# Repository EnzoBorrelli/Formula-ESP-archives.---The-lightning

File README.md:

# Formula-ESP-archives.---The-lightning
que hacer= descripcion

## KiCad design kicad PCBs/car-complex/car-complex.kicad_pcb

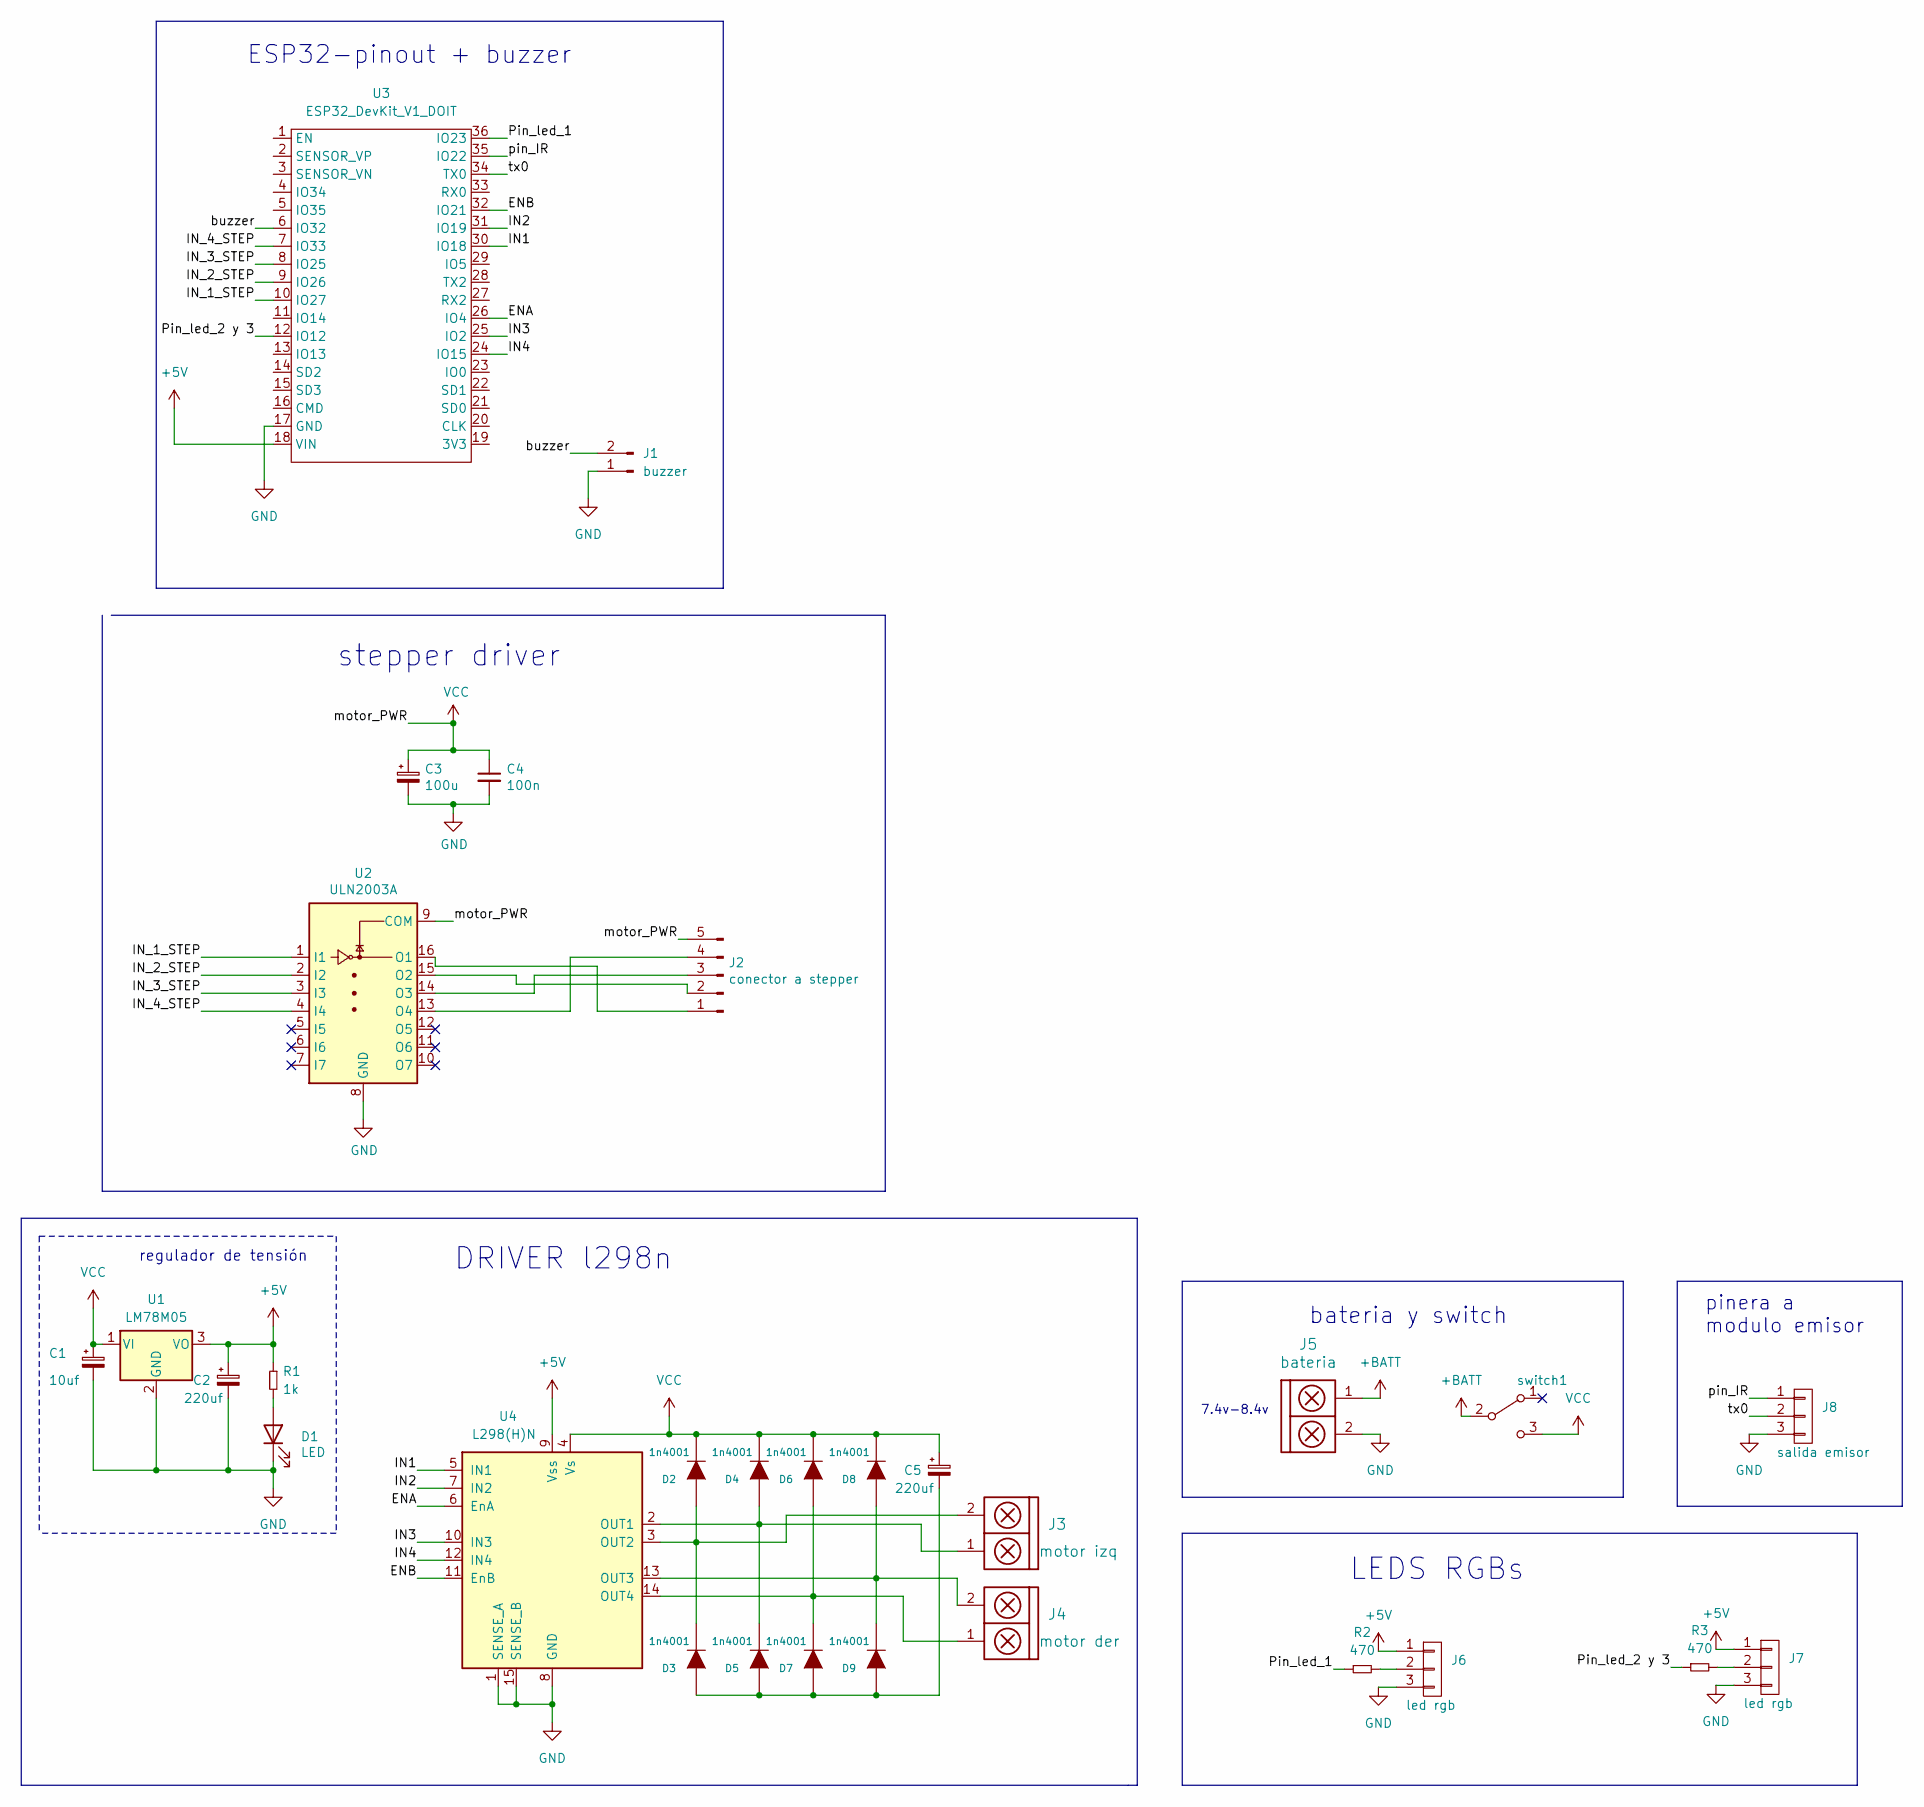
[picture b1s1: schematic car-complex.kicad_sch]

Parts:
C1: 10uf; CP_Radial_D5.0mm_P2.00mm
C2, C5: 220uf; CP_Radial_D5.0mm_P2.00mm
C3: 100u; CP_Radial_D5.0mm_P2.00mm
C4: 100n; C_Rect_L4.6mm_W2.0mm_P2.50mm_MKS02_FKP02
D1: LED; led_3mm_clear
D2, D3, D4, D5, D6, D7, D8, D9: 1n4001; DO-41
J1: buzzer; Pin_strip_2
J2: conector a stepper; JST_EH_B5B-EH-A_1x05_P2.50mm_Vertical
J3: motor izq; BORNERA2_AZUL
J4: motor der; BORNERA2_AZUL
J5: bateria; BORNERA2_AZUL
J6, J7: led rgb; JST_EH_B3B-EH-A_1x03_P2.50mm_Vertical
J8: salida emisor; JST_EH_B3B-EH-A_1x03_P2.50mm_Vertical
R1: 1k; RES0.3
R2, R3: 470; RES0.3
U1: LM78M05; TO-220-3_Vertical
U2: ULN2003A; DIP-16_W7.62mm
U3: ESP32_DevKit_V1_DOIT; ESP32_DEVKIT_V1_DOIT
U4: L298(H)N; TO-220-15_P2.54x2.54mm_StaggerEven_Lead4.58mm_Vertical
switch1: SW_SPDT; SW_SPDT_TH_Vertical

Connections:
+5V: C2.1, J6.1, J7.1, R1.1, U1.3 (VO), U3.18 (VIN), U4.9 (Vss)
+BATT: J5.1, switch1.2 (B)
/ENA: U3.26 (IO4), U4.6 (EnA)
/ENB: U3.32 (IO21), U4.11 (EnB)
/IN1: U3.30 (IO18), U4.5 (IN1)
/IN2: U3.31 (IO19), U4.7 (IN2)
/IN3: U3.25 (IO2), U4.10 (IN3)
/IN4: U3.24 (IO15), U4.12 (IN4)
/IN_1_STEP: U2.1 (I1), U3.10 (IO27)
/IN_2_STEP: U2.2 (I2), U3.9 (IO26)
/IN_3_STEP: U2.3 (I3), U3.8 (IO25)
/IN_4_STEP: U2.4 (I4), U3.7 (IO33)
/Pin_led_1: R2.1, U3.36 (IO23)
/Pin_led_2 y 3: R3.1, U3.12 (IO12)
/buzzer: J1.2, U3.6 (IO32)
/pin_IR: J8.1, U3.35 (IO22)
/tx0: J8.2, U3.34 (TX0)
GND: C1.2, C2.2, C3.2, C4.2, D1.1 (K), J1.1, J5.2, J6.3, J7.3, J8.3, U1.2 (GND), U2.8 (GND), U3.17 (GND), U4.1 (SENSE_A), U4.8 (GND), U4.15 (SENSE_B)
unnamed: C5.2, D3.1 (A), D5.1 (A), D7.1 (A), D9.1 (A)
unnamed: D1.2 (A), R1.2
unnamed: D2.1 (A), D3.2 (K), J3.2, U4.3 (OUT2)
unnamed: D4.1 (A), D5.2 (K), J3.1, U4.2 (OUT1)
unnamed: D6.1 (A), D7.2 (K), J4.1, U4.14 (OUT4)
unnamed: D8.1 (A), D9.2 (K), J4.2, U4.13 (OUT3)
unnamed: J2.1, U2.16 (O1)
unnamed: J2.2, U2.15 (O2)
unnamed: J2.3, U2.14 (O3)
unnamed: J2.4, U2.13 (O4)
unnamed: J6.2, R2.2
unnamed: J7.2, R3.2
VCC: C1.1, C3.1, C4.1, C5.1, D2.2 (K), D4.2 (K), D6.2 (K), D8.2 (K), J2.5, U1.1 (VI), U2.9 (COM), U4.4 (Vs), switch1.3 (C)

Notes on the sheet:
stepper driver
7.4v-8.4v
regulador de tensión
LEDS RGBs
ESP32-pinout + buzzer
DRIVER l298n
bateria y switch
pinera a modulo emisor

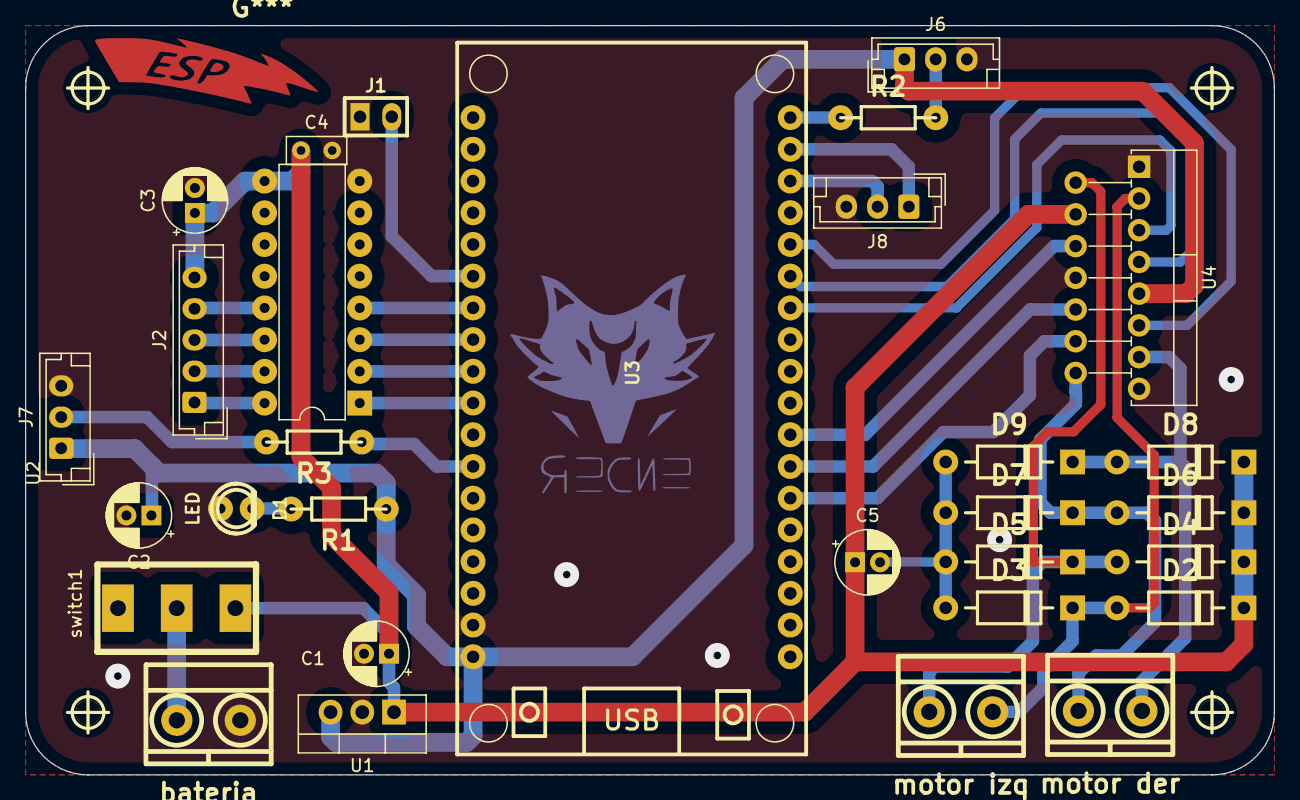
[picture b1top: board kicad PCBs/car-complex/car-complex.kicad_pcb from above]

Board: 2 copper layers, 100.0 x 60.0 mm, 34 parts (0 on the bottom side), 31 nets.

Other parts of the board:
hole_2mm, hole_2mm#2, hole_2mm#3, hole_2mm#4: VAL**; hole_2mm

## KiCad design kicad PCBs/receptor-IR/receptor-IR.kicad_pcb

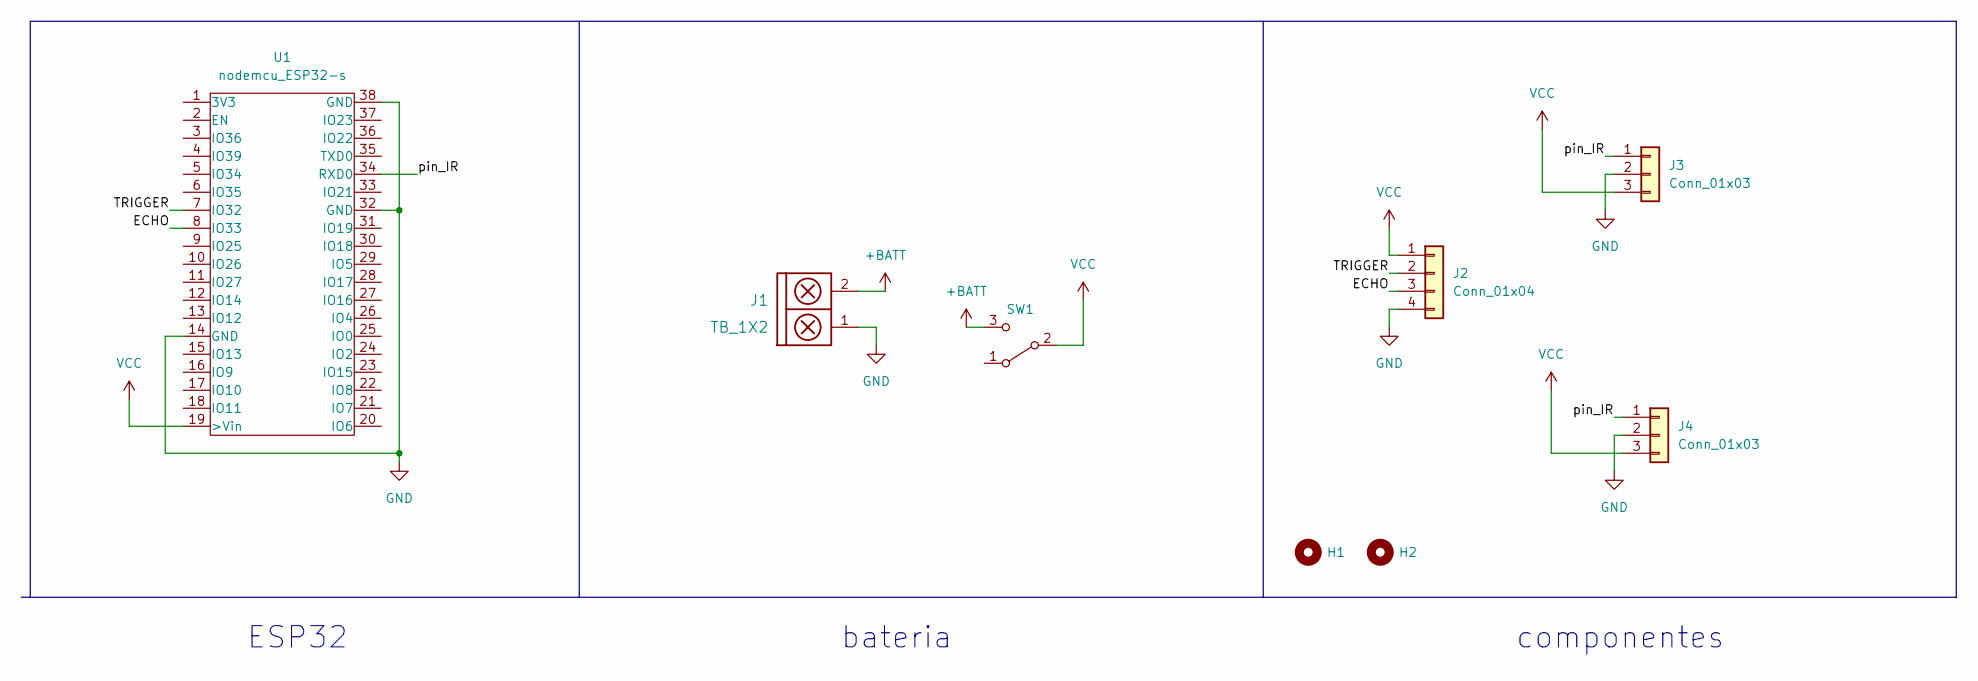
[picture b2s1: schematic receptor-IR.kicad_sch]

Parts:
H1, H2: Mounting_Hole; hole_3mm
J1: TB_1X2; BORNERA2_AZUL
J2: Conn_01x04; pin_strip_4
J3, J4: Conn_01x03; Pin_Header_3
SW1: SW_SPDT; SW_SPDT_TH_Vertical
U1: nodemcu_ESP32-s; ESP32S

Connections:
+BATT: J1.2, SW1.3 (C)
/ECHO: J2.3, U1.8 (IO33)
/TRIGGER: J2.2, U1.7 (IO32)
/pin_IR: J3.1, J4.1, U1.34 (RXD0)
GND: J1.1, J2.4, J3.2, J4.2, U1.14 (GND), U1.32 (GND), U1.38 (GND)
VCC: J2.1, J3.3, J4.3, SW1.2 (B), U1.19 (>Vin)

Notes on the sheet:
componentes
bateria
ESP32

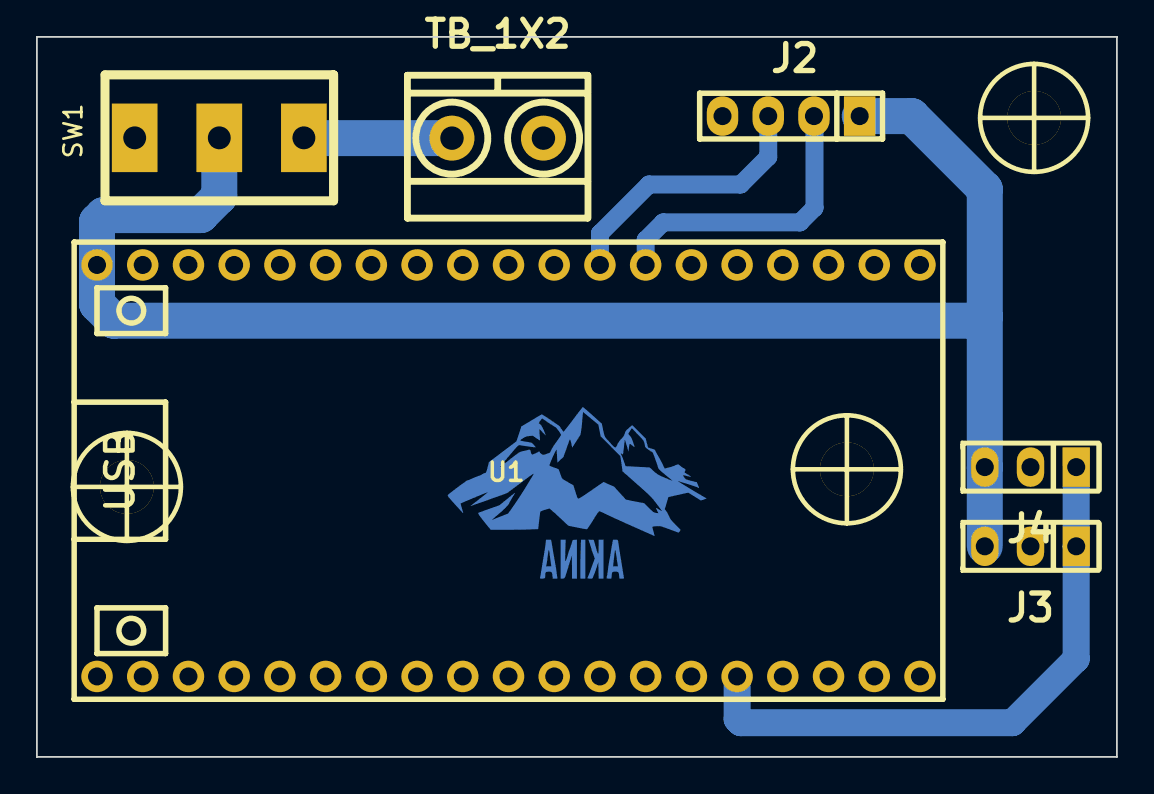
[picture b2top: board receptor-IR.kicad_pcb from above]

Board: 2 copper layers, 60.0 x 40.0 mm, 9 parts (0 on the bottom side), 6 nets.

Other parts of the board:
H2#2: Mounting_Hole; hole_3mm

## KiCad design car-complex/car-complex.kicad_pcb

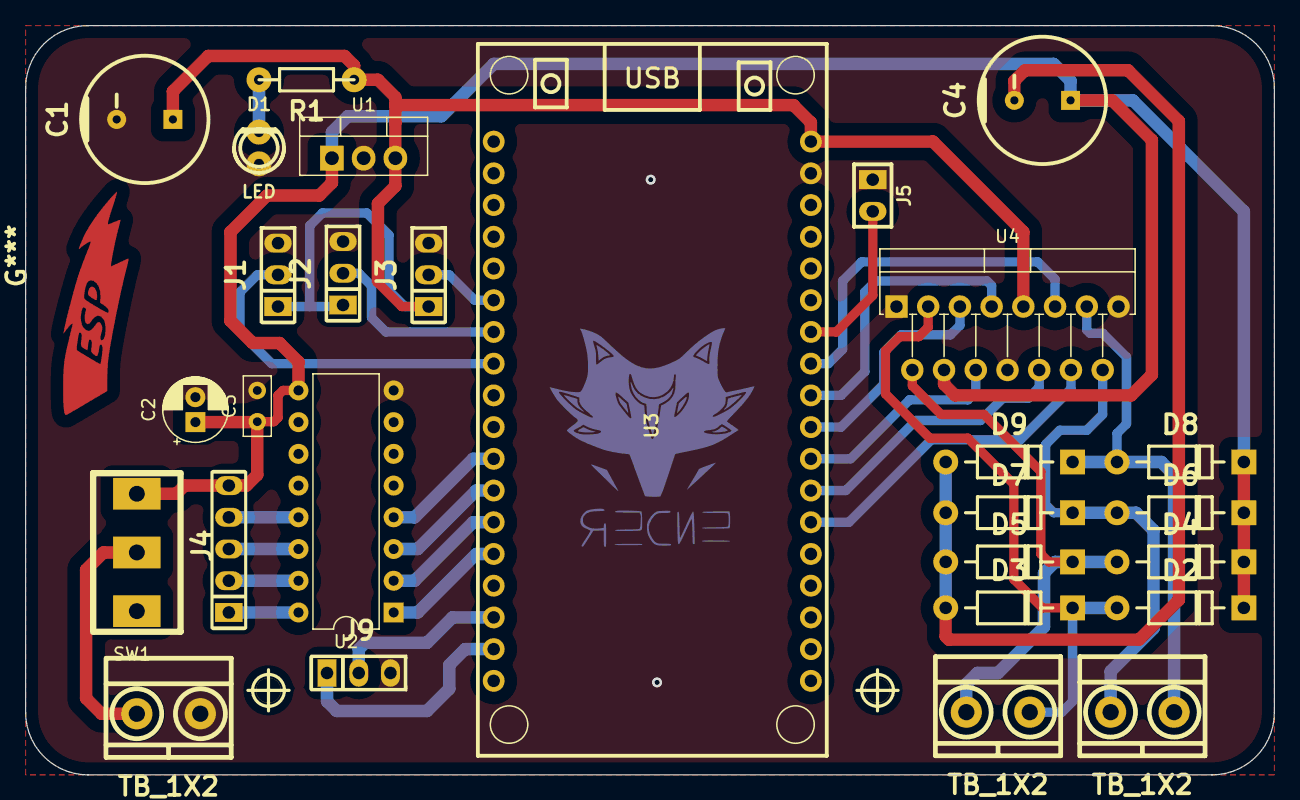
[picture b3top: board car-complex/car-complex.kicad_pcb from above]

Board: 2 copper layers, 100.0 x 60.0 mm, 30 parts (0 on the bottom side), 30 nets.

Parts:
C1, C4: 220uf; CAP_ELEC_10X8mm
C2: 100u; CP_Radial_D5.0mm_P2.00mm
C3: 100n; C_Rect_L4.6mm_W2.0mm_P2.50mm_MKS02_FKP02
D1: LED; led_3mm_clear
D2, D3, D4, D5, D6, D7, D8, D9: DIODE; DO-41
J1, J2, J3: led rgb; Pin_Header_3
J4: Conn_01x05_Male; Pin_Strip_5
J5: buzzer; Pin_strip_2
J6, J7, J8: TB_1X2; BORNERA2_AZUL
J9: salida emisor; Pin_Header_3
R1: R; RES0.3
SW1: SW_SPDT; SW_SPDT_TH_Vertical
U1: LM78M05; TO-220-3_Vertical
U2: ULN2003A; DIP-16_W7.62mm
U3: ESP32_DevKit_V1_DOIT; ESP32_DEVKIT_V1_DOIT
U4: L298(H)N; TO-220-15_P2.54x2.54mm_StaggerEven_Lead4.58mm_Vertical
hole_2mm, hole_2mm#2: VAL**; hole_2mm

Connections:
+5V: C1.1, J1.1, J2.1, J3.1, R1.1, U1.3 (VO), U3.18 (VIN), U4.9 (Vss)
+BATT: J8.1, SW1.2 (B)
/ENA: U3.8 (IO25), U4.6 (EnA)
/ENB: U3.11 (IO14), U4.11 (EnB)
/IN1: U3.9 (IO26), U4.5 (IN1)
/IN2: U3.10 (IO27), U4.7 (IN2)
/IN3: U3.7 (IO33), U4.10 (IN3)
/IN4: U3.6 (IO32), U4.12 (IN4)
/IN_1_STEP: U2.1 (I1), U3.32 (IO21)
/IN_2_STEP: U2.2 (I2), U3.31 (IO19)
/IN_3_STEP: U2.3 (I3), U3.30 (IO18)
/IN_4_STEP: U2.4 (I4), U3.29 (IO5)
/Pin_led_1: J1.2, U3.26 (IO4)
/Pin_led_2: J2.2, U3.25 (IO2)
/Pin_led_3: J3.2, U3.24 (IO15)
/buzzer: J5.2, U3.12 (IO12)
/pin_IR: J9.1, U3.35 (IO22)
/tx0: J9.2, U3.34 (TX0)
GND: C1.2, C2.2, C3.2, D1.1 (K), J1.3, J2.3, J3.3, J5.1, J8.2, J9.3, U1.2 (GND), U2.8 (GND), U3.17 (GND), U4.1 (SENSE_A), U4.8 (GND), U4.15 (SENSE_B)
unnamed: C4.2, D3.1 (A), D5.1 (A), D7.1 (A), D9.1 (A)
unnamed: D1.2 (A), R1.2
unnamed: D2.1 (A), D3.2 (K), J6.2, U4.3 (OUT2)
unnamed: D4.1 (A), D5.2 (K), J6.1, U4.2 (OUT1)
unnamed: D6.1 (A), D7.2 (K), J7.1, U4.14 (OUT4)
unnamed: D8.1 (A), D9.2 (K), J7.2, U4.13 (OUT3)
unnamed: J4.1, U2.16 (O1)
unnamed: J4.2, U2.15 (O2)
unnamed: J4.3, U2.14 (O3)
unnamed: J4.4, U2.13 (O4)
VCC: C2.1, C3.1, C4.1, D2.2 (K), D4.2 (K), D6.2 (K), D8.2 (K), J4.5, SW1.3 (C), U1.1 (VI), U2.9 (COM), U4.4 (Vs)

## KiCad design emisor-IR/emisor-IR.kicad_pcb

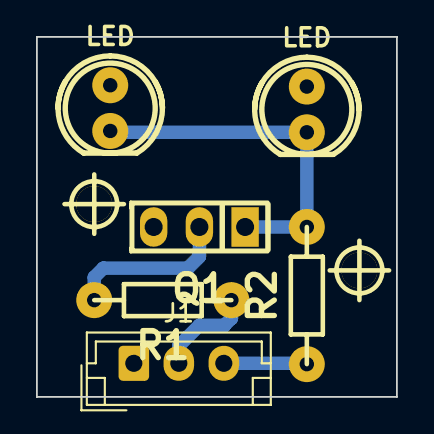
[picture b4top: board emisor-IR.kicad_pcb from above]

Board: 2 copper layers, 20.0 x 20.0 mm, 8 parts (0 on the bottom side), 5 nets.

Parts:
D1, D2: LED; led_5mm_clear
H1, H2: Mounting_Hole; hole_2mm
J1: Conn_01x03; JST_EH_B3B-EH-A_1x03_P2.50mm_Vertical
Q1: BC548; Pin_Header_3
R1, R2: R; RES0.3

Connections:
Earth: D1.1 (K), D2.1 (K), J1.1, Q1.3 (E)
unnamed: D1.2 (A), D2.2 (A), Q1.1 (C), R2.2
unnamed: J1.2, R1.1
unnamed: J1.3, R2.1
unnamed: Q1.2 (B), R1.2

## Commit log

2022-09-07 uploaded all the currently files off the project
2022-09-07 tests de features a incluir en el codigo principal
2022-09-07 se ordenaron los archivos de manera mas ordenada
2022-09-07 se agrega el archivo principal de codigo (WIP)
2022-09-07 actualizaciones menores
2022-09-07 codigo de modulo emisor_IR
2022-09-19 actualización 19/09/2022
2022-09-21 actualización menor, 21/9/22
2022-09-25 actualización 25/9/22
2022-10-26 actualizacion 26/10/22
